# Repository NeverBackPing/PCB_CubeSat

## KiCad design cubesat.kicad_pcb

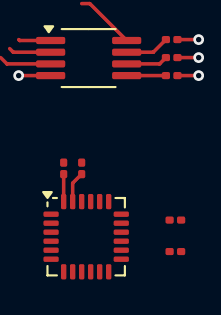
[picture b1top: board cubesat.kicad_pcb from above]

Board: 2 copper layers, 9 parts (0 on the bottom side), 9 nets.

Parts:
R1, R2, R3: 10k; R_0201_0603Metric
R4, R5, R6, R7: 4.7k; R_0201_0603Metric
U1: MCP9808_MSOP; MSOP-8_3x3mm_P0.65mm
U2: MPU-6050; InvenSense_QFN-24_4x4mm_P0.5mm

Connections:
+3V3: R4.2, R5.1, R6.2, R7.2, U2.8 (VLOGIC), U2.13 (VDD)
GND: R1.2, R2.1, R3.1, U1.4 (GND), U2.1 (CLKIN), U2.11 (FSYNC), U2.18 (GND)
unnamed: R1.1, U1.7 (A0)
unnamed: R2.2, U1.6 (A1)
unnamed: R3.2, U1.5 (A2)
unnamed: R6.1, U2.7 (AUX_CL)
unnamed: R7.1, U2.6 (AUX_DA)
unnamed: R5.2, U2.23 (SCL)
unnamed: R4.1, U2.24 (SDA)

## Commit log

2025-08-10 start
2025-08-10 cubesat-backups
2025-08-10 add mpu schéma
